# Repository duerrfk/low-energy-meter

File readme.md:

# What is Low-Energy-Meter?

Low-Energy-Meter is a tool for measuring the energy consumption of low-energy devices using a Raspberry Pi. In particular, it was developed to measure the energy consumption of battery-powered Bluetooth Low Energy (BLE) devices.

Low-energy devices switch frequently between active mode and power-save mode striving for minimum duty cycles. The energy consumption differs significantly by several orders of magnitude between active mode and power-save mode (milli-amps vs. micro-amps). This makes energy measurements challenging. For instance, it is hard to dimension a shunt resistor for measuring the voltage drop along the resistor to calculate current as I = V/R. If the shunt resistor is optimized for active mode, the voltage drop will be very low in power-save mode and thus hard to measure. If the shunt resistor is optimized for power-save mode, the voltage drop will be very large in active mode, and the device only runs at significantly reduced voltage possibly dropping below the threshold where brownout reset engages. 

Therefore, we use a different method to measure the energy consumption. We use a large capacitor (C = 10000 uF) as power supply. The energy stored in a capacitor can be calculated as E = 0.5\*C\*V^2. Thus, knowing the time period (t) that it takes to drop from a certain initial voltage (V_upper) to a certain lower voltage (V_lower), we can calculate the energy consumed in period t as E_delta = 0.5\*C\*(V_upper^2-V_lower^2) and the average power consumption as P_avg = E_delta/t. The energy consumption naturally includes the energy spent in active mode as well as power-save mode. So the basic idea is to first charge the capacitor from a "real" power supply (voltage regulator of the Raspberry Pi) and then discharge the capacitor via the device under test. While discharging, we periodically measure the voltage of the capacitor. When the voltage drops below a certain threshold somewhere above the critical brownout detection threshold, we automatically charge the capacitor again and start a new measuring cycle. 

One might argue that the capacitor is prone to self-discharging. However, experiments showed that this effect is very small, even smaller than the energy consumption in power-save mode and much smaller than the energy consumption in active mode, and thus negligible for our purpose. TODO: Prove this claim.

Low-Energy-Meter consists of two parts:

* Measurement hardware connected to the Raspberry Pi. The measurement hardware is basically a circuit board (PCB) with an analog-to-digital converter (ADC), the 10000 uF supply capacitor and some more components to support automatic measurements by repeatedly charging the supply capacitor and sampling the capacitor voltage while discharging the capacitor. The measurement board is depicted in the images below with a simple resistor connected as load ("device under test"). Schematics and PCB layout of the PCB are included.
* Software for the Raspberry Pi that automates the process of charging and sampling the supply capacitor and logging samples to the SD card.

# The Hardware: Measurement Board

We use a capacitor of 10000 uF to power the device under test. This is large enough to run a BLE device for several minutes (using reasonable power-saving techniques) while voltage drops from say 3.0 V to 2.0 V. This capacitor is charged via a 160 Ohm resistor making sure not to overload the 3.3 V power rail of the Raspberry Pi. Since we charge the capacitor from the 3.3 V rail, 3.3 V is the maximum voltage we can supply to the device under test. For the BLE target devices and most MCUs this is a suitable voltage.
 
The measurement board is connected to a Raspberry Pi Model B (a single core Pi is good enough for 1 kHz sampling rate). It includes a 12 bit ADC (MCP6008 or MCP6004) to sample the voltage of the supply capacitor and transmit voltage samples to the Raspberry Pi via SPI.

Moreover, it includes two relays, one for charging the capacitor and powering the device under test while charging, and one for connecting the supply capacitor to the device under test when the capacitor has been charged for measuring the energy consumption. Both relays are controlled from two GPIOs of the Raspberry Pi to automate the process of charging and sampling while discharging the capacitor. An ULN2803 is used to drive the relays. 

A precise 2.5 V voltage reference (LM385) is used as reference for the ADC.

The board layout is optimized for simple etching (alternatively, you can send the Gerber files to a PCB manufacturer of your choice). Moreover, we only use easily available standard components. 

# The Software

Low-Energy-Meter includes a command line tool to automate the process of charging and sampling the supply capacitor and logging samples to a file.

The software tool called low-energy-meter can be found in folder src. 

## Compiling Low-Energy-Meter Tool

As a prerequisite, you need the [bcm2835 library](http://www.airspayce.com/mikem/bcm2835/). After installing the library, you can compile the tool with the following command:

    $ make low-energy-meter

## Running Low-Energy-Meter Tool

For precise sampling intervals, we recommend to use the RTPREEMPT patch for Linux (instructions on how to compile an RTPREEMPT kernel can be found on [this web-site](http://www.frank-durr.de/?p=203). 

The command line tool uses the following arguments:

* ```-f SAMPLING_FREQUENCY```: Sampling frequency. 1 kHz seems to be a safe upper bound where the Raspberry Pi can still deterministically meet the 1 ms sampling interval.
* ```-o FILE```: Output file for logging samples.
* ```-l THRESHOLD_LOWER```: Lower voltage threshold (ADC count) defining when the supply capacitor is recharged.
* ```-u THRESHOLD_UPPER```: Upper threshold (ADC count) defining when a discharging (sampling) cycle starts.

ADC counts can be translated to voltage thresholds as follows: V = 5.0 V \* 4095/ADCCount

Note that the reference voltage of the ADC is 2.5 V and we divide the voltage sampled by the ADC by 2 to stay within the allowed voltage range of max. 2.5 V. Therefore, an ADC count of 4095 corresponds to 5 V.  
    
The format of the output file is CSV (comma-separated values) with the following values per sample: 

* Timestamp of the sample in nanoseconds.
* Epoch (discharging cycle). Measurements are only recorded while discharging, i.e., while powering the device under test from the capacitor.
* ADC count, which can be translated to capacitor voltage by calculating V = 5.0 V \* 4095/ADCCount.

# Measurement Example

The following example shows how to take measurements, and how to evaluate them using [R](https://www.r-project.org/). In this example, we measure the energy-efficiency of the [Faros]() Bluetooth Low Energy Beacon implementing Google's Eddystone standard. The data of this experiment is available in folder data. 

## Step 1: Taking measurements

We take measurements with 1000 Hz sampling frequency, and lower and upper voltage thresholds of 2.0 V (ADC count = 2.0 V / 5.0 V \* 4095 = 1638) and 3.2 V (ADC count = 2621), respectively, i.e., the device under test is running from voltages in this range. The Faros beacon can be operated down to 1.8 V, so re-charging the capacitor at 2.0 V leaves enough headroom to ensure that the beacon will not reset. We also provide the data set of this experiment in folder data, so you can follow the steps below.

    $ sudo ./low-energy-meter -f 1000 -l 1638 -u 2621 -o faros.csv -p 80

## Step 2: Loading the CSV data into R.

    $ R
    $ x <- read.csv(file="faros.csv",head=FALSE,sep=",")

After this step, you will find all data in data frame x, which is basically a table with three rows called x$V1 (timestamp in nanoseconds), x$V2 (measurement cycle), and x$V3 (ADC count of voltage measurements).

## Step 3: Selecting data for evaluation

We will select data from one measurement cycle in a certain voltage range between 2.0 V (ADC count 1638) and 3.0 V (ADC count 2457).

    $ y = subset(x, x$V2==2 & x$V3 >= 1638 & x$V3 <= 2457)

The selected data is now in data frame y. For visual inspection, you can plot the voltage (ADC counts) over time using the following command:

    $ plot(y$V1/1000000000-min(y$V1)/1000000000, y$V3/4095*5.0, xlab="t [s]", ylab="Voltage [V]")

The following plot shows the measurements taken for the Faros beacon.

## Step 4: Calculating consumed energy and average power consumption

First, we determine the maximum and minumum voltage of the selected sample interval:

    $ max(y$V3)
    [1] 2457
    $ min(y$V3)
    [1] 1638

So the maximum and minumum voltages are V_max = 2457/4095 \* 5.0 V = 3.0 V and V_min = 1638/4095 \* 5.0 V = 2.0 V, respectively.

Then, we calculate the time t that it took to drop from V_max to V_min:

    $ (max(y$V1)-min(y$V1))/1000000000
    151.715
 
So it took t = 151.715 s.

Since we know the capacity of the supply capacitor (10000 uF), we can calculatete the energy spent in this time interal as:

E = 0.5\*10000 uF\*(3.0 V)^2 - 0.5\*10000 uF\*(2.0 V)^2 = 0.025 J

The average power consumption is then calculated as:

P_avg = E/t = 0.025 J / 151.715 s = 164.78 uW

So if the Faros BLE beacon is powered from AA-size batteries (two connected in series to provide a nominal voltage of 3.0 V) with say 2.60 Wh energy, the beacon could run for about 657 days or 1.8 years.

# Voltage Leakage

One might argue that this measurement method is prone to inaccuracies because of self-discharging effects, bias current flowing into or out of the opamp connected to the capacitor (which according to the datasheet of the MCP6001 should be in the order of pA, so possibly not the biggest effect), etc. In order to evaluate these undesired effects, we took measurements without any load connected, where we would expect (ideally) the power consumption to be zero. The data is included in the data folder. The figure below depicts the result.

We can see that the capacitor discharged from initially V_max = 3.300 V to V_min = 3.066 V over a time period of t = 27926 s = 7.76 h. Hence, the energy consumed in this period is 0.0074 J, and the average power consumption is 266.713 nW. So giving some safety-margin, we can assume an accuracy of power measurements of about 1 uW. 

# Limitations

This measurement method is targeting low-energy devices, in particular, BLE devices. We make the following assumptions:

* The device under test can run from varying voltages in a range from 3.3 V to some lower threshold. Typical lower thresholds of MCUs used in BLE devices are as low as 1.8 V. For devices requiring more than 3.3 V (like for instance a Raspberry Pi, which is powered from 5.0 V USB), the circuit is not suitable.
* The device under test consumes little power up to tens of milliamps over the desired voltage range. Otherwise, the supply capacitor does not provide enough energy to run the device for a longer period including all operational modes (active and power-save mode). Up to tens of milliamps are typical values for active BLE devices with active MCU and radio (in power-save mode, the current is much lower down to micro-amps).    

# Licensing

Low-Energy-Meter uses two licenses for open hardware and software, respectively:

* The software (source code) is licensed under the Apache License 2.0
* The hardware (schematic diagrams, circuit board layouts, hardware documentation) is licensed under the CERN Open Hardware Licence v1.2

Both licenses are included in the repository.

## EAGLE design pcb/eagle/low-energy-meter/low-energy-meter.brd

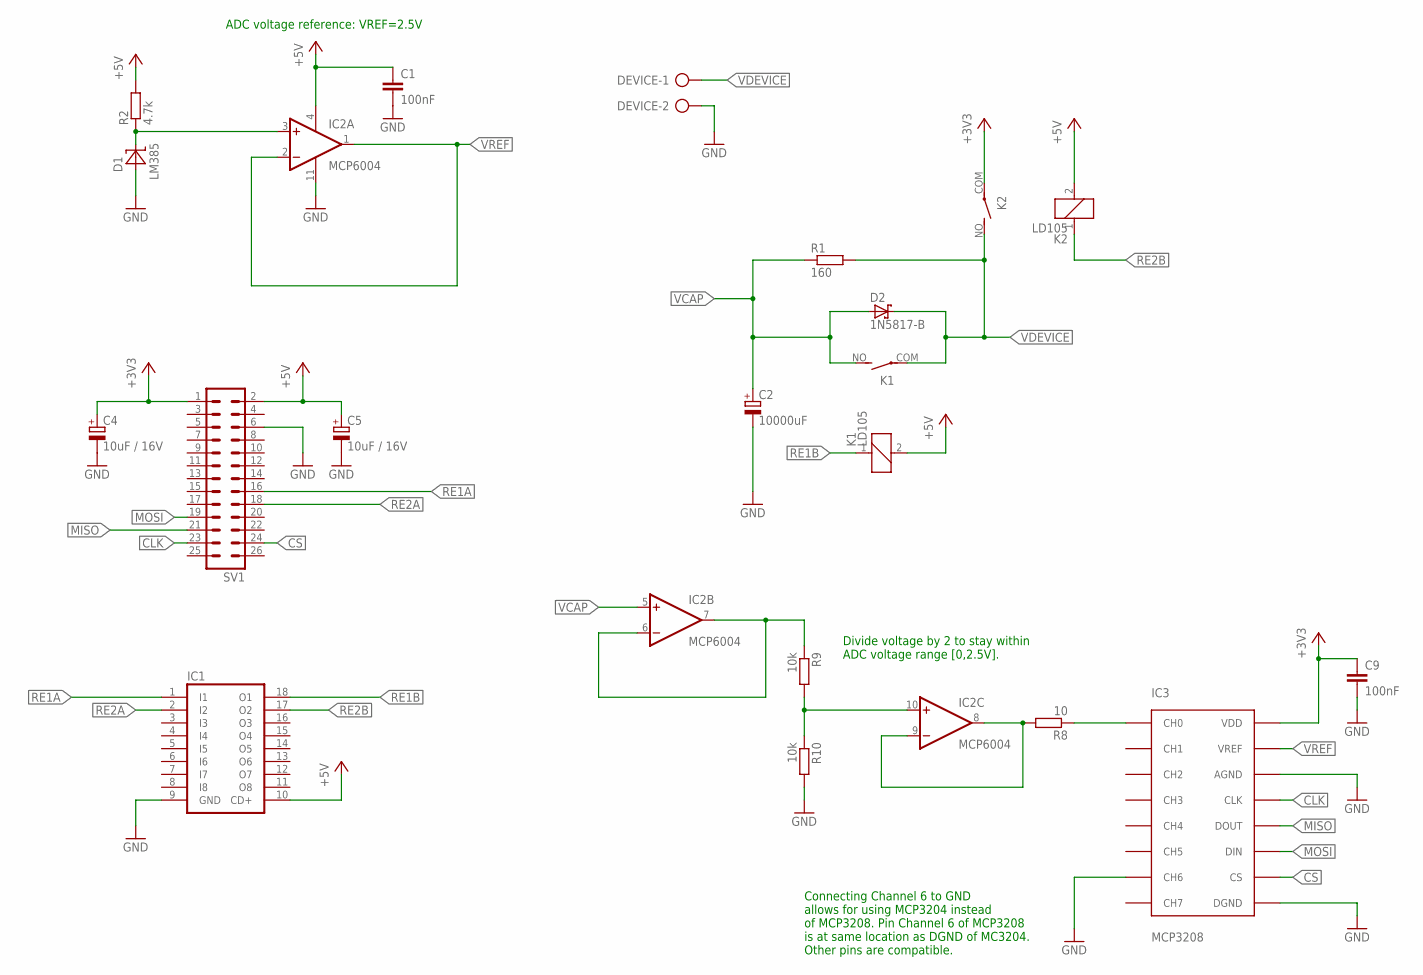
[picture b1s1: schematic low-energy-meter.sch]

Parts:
C1, C9: 100nF; C050-024X044
C2: 10000uF; E7,5-18
C4, C5: 10uF / 16V; E2,5-6
D1: LM385; TO-92
D2: 1N5817-B; DO41-7.6
DEVICE: AK500/2
IC1: ULN2803A; DIL18
IC2: MCP6004; DIL14
IC3: MCP3208; DIL16
K1, K2: LD105; LD
R1: 160; 0207/7
R2: 4.7k; 0207/7
R8: 10; 0207/7
R9, R10: 10k; 0207/7
SV1: ML26

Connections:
+3V3: C4.+, C9.1, IC3.VDD, K2.COM, SV1.1
+5V: C1.1, C5.+, IC1.10 (CD+), IC2.4 (V+), K1.2, K2.2, R2.2, SV1.2
CLK: IC3.CLK, SV1.23
CS: IC3.CS, SV1.24
GND: C1.2, C2.-, C4.-, C5.-, C9.2, D1.+, DEVICE.2, IC1.9 (GND), IC2.11 (V-), IC3.AGND, IC3.CH6, IC3.DGND, R10.2, SV1.6
MISO: IC3.DOUT, SV1.21
MOSI: IC3.DIN, SV1.19
unnamed: IC2.6 (-IN), IC2.7 (OUT), R9.1
unnamed: IC2.10 (+IN), R9.2, R10.1
unnamed: IC3.CH0, R8.1
unnamed: IC2.8 (OUT), IC2.9 (-IN), R8.2
unnamed: D1.-, IC2.3 (+IN), R2.1
RE1A: IC1.1 (I1), SV1.16
RE1B: IC1.18 (O1), K1.1
RE2A: IC1.2 (I2), SV1.18
RE2B: IC1.17 (O2), K2.1
VCAP: C2.+, D2.A, IC2.5 (+IN), K1.NO (S), R1.1
VDEVICE: D2.C, DEVICE.1, K1.COM, K2.NO (S), R1.2
VREF: IC2.1 (OUT), IC2.2 (-IN), IC3.VREF

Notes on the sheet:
ADC voltage reference: VREF=2.5V
Divide voltage by 2 to stay within ADC voltage range [0,2.5V].
Connecting Channel 6 to GND allows for using MCP3204 instead of MCP3208. Pin Channel 6 of MCP3208 is at same location as DGND of MC3204. Other pins are compatible.

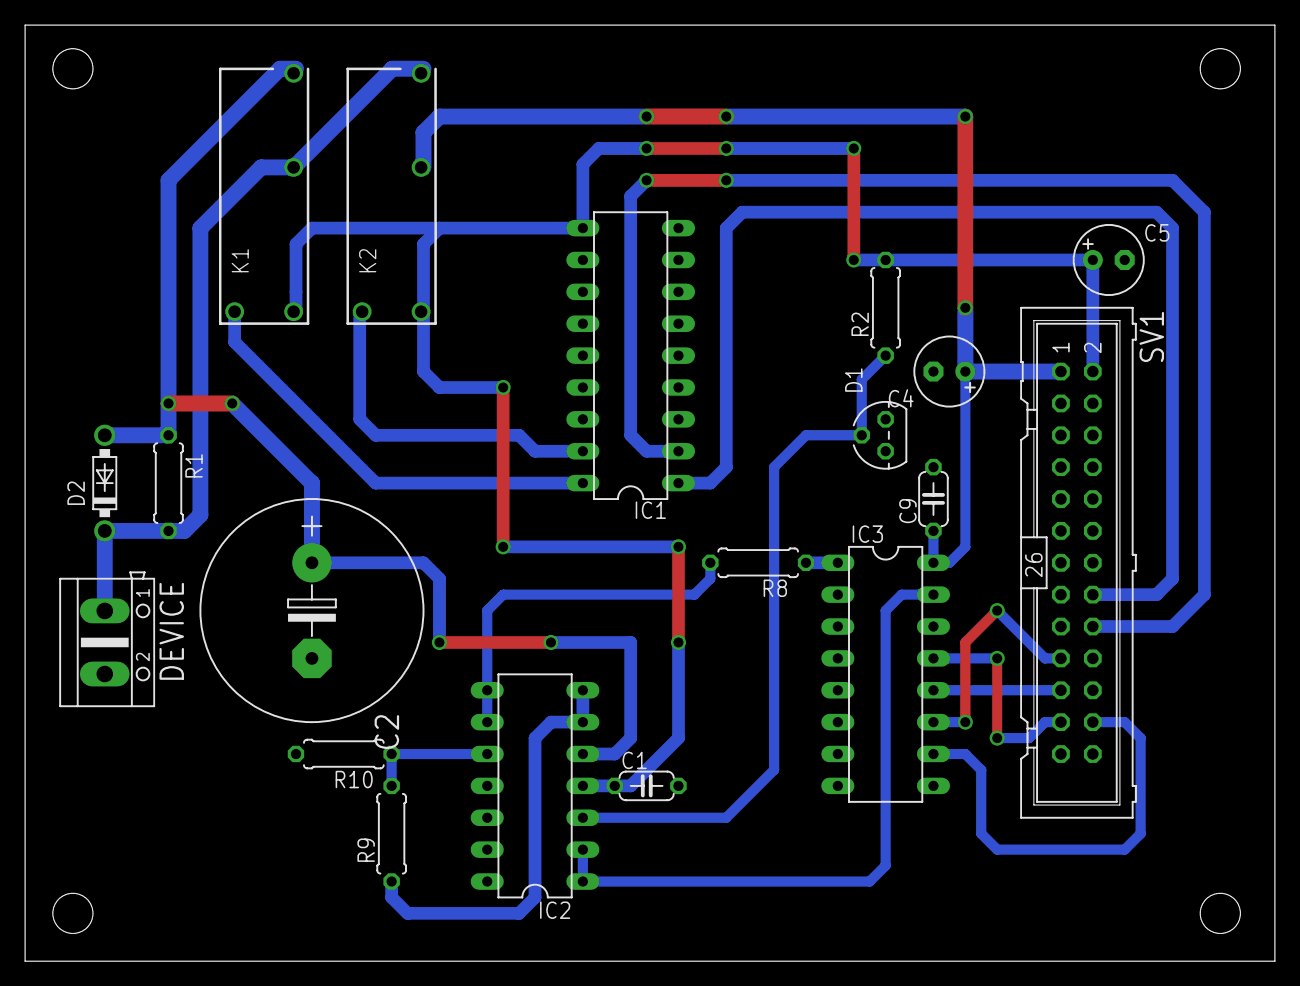
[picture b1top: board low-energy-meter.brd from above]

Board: 2 copper layers, 99.6 x 74.6 mm, 19 parts (0 on the bottom side), 19 nets.

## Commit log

2016-05-28 Initial check-in
2016-05-28 Added image showing self-discharging effect
2016-05-28 Corrected image
